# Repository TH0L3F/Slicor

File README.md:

# Slicor
Trancheuse de sable pour conçue pour l'université de Lille

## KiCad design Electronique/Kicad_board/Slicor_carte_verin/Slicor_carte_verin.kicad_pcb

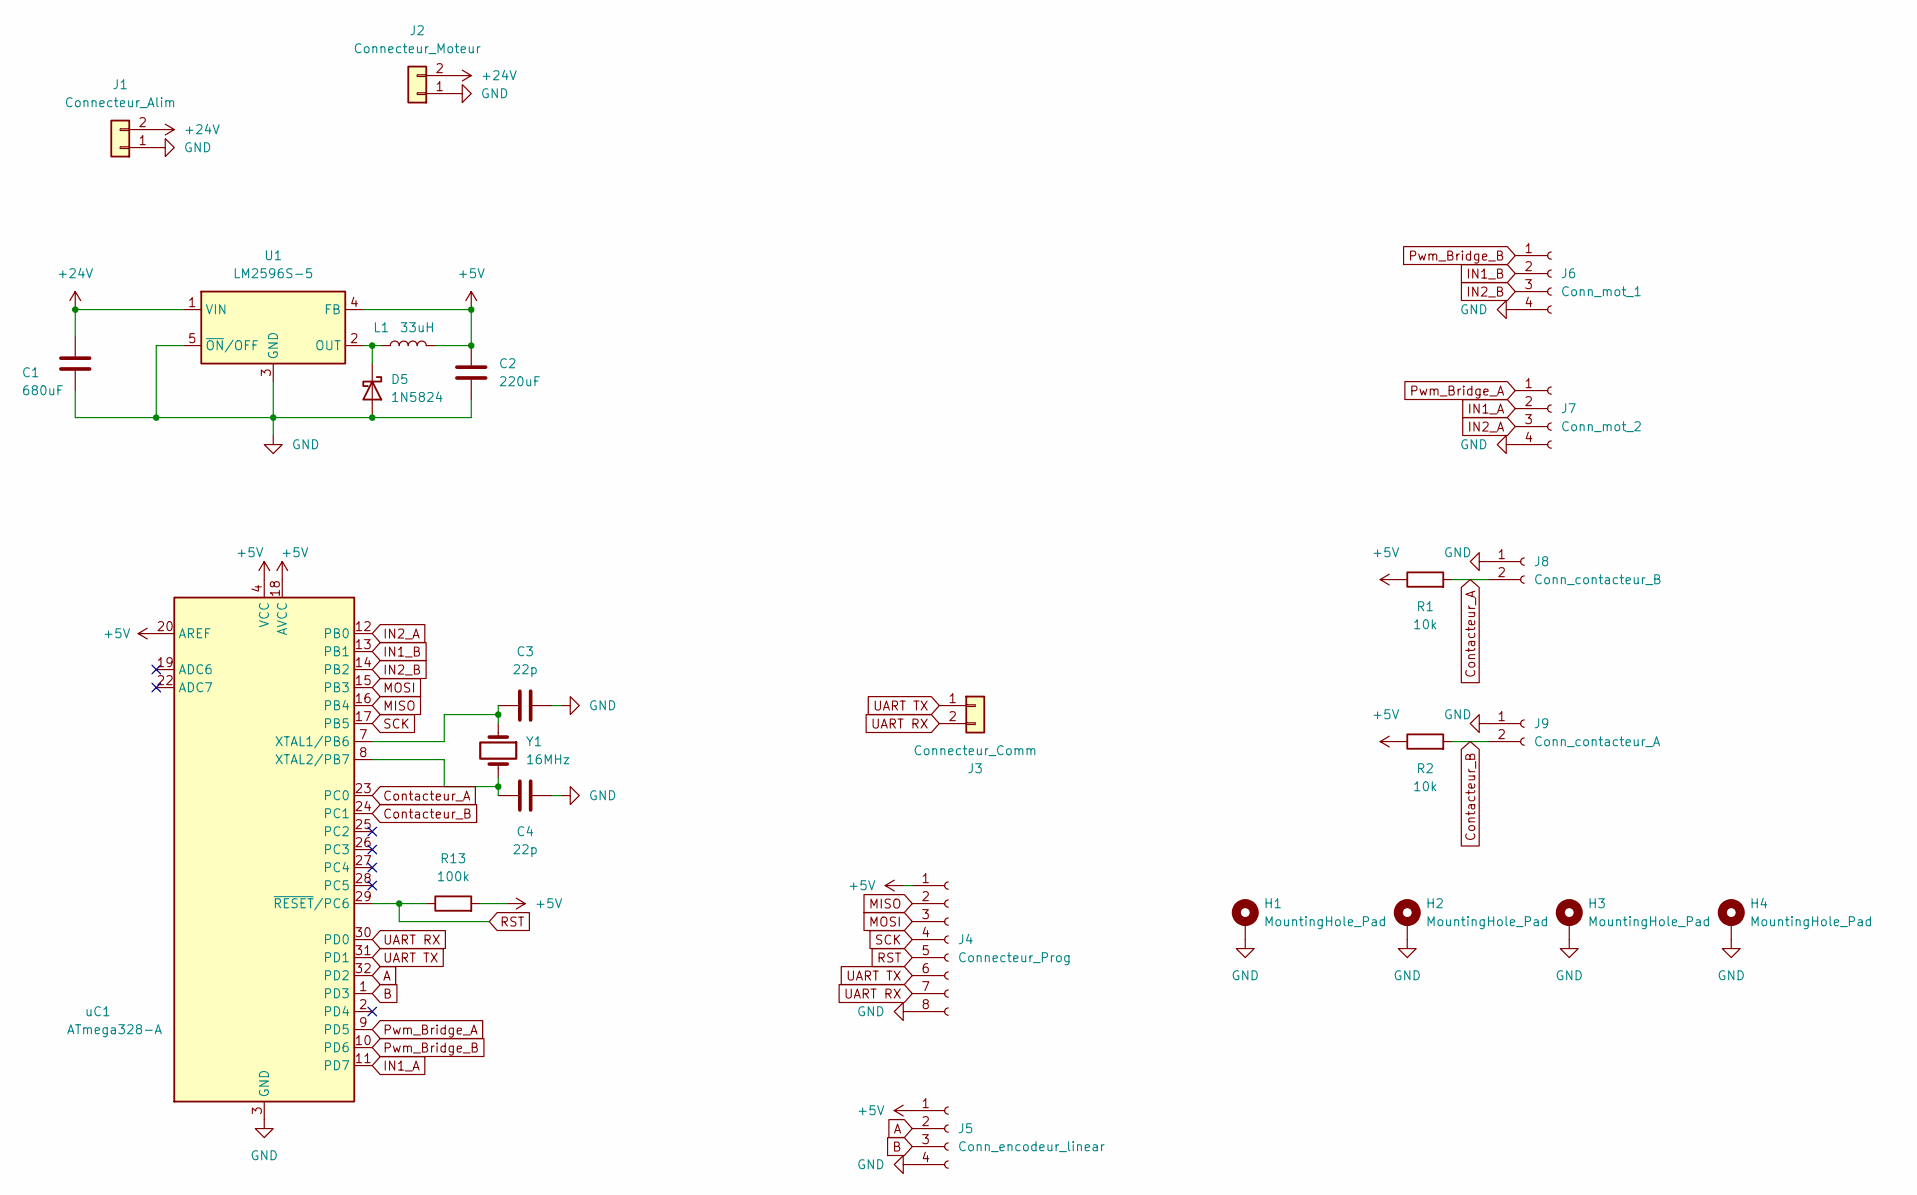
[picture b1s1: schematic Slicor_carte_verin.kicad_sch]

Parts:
C1: 680uF; C_Elec_10x10.2
C2: 220uF; C_Elec_10x10.2
C3, C4: 22p; C_01005_0402Metric
D5: 1N5824; D_SOD-128
H1, H2, H3, H4: MountingHole_Pad; MountingHole_4mm_Pad_Via
J1: Connecteur_Alim; TerminalBlock_bornier-2_P5.08mm
J2: Connecteur_Moteur; TerminalBlock_bornier-2_P5.08mm
J3: Connecteur_Comm; JST_XH_B2B-XH-A_1x02_P2.50mm_Vertical
J4: Connecteur_Prog; PinHeader_1x08_P2.54mm_Vertical
J5: Conn_encodeur_linear; JST_XH_B4B-XH-A_1x04_P2.50mm_Vertical
J6: Conn_mot_1; JST_XH_B4B-XH-A_1x04_P2.50mm_Vertical
J7: Conn_mot_2; JST_XH_B4B-XH-A_1x04_P2.50mm_Vertical
J8: Conn_contacteur_B; JST_XH_B2B-XH-A_1x02_P2.50mm_Vertical
J9: Conn_contacteur_A; JST_XH_B2B-XH-A_1x02_P2.50mm_Vertical
L1: 33uH; L_7.3x7.3_H4.5
R1, R2: 10k; R_1206_3216Metric
R13: 100k; R_1206_3216Metric
U1: LM2596S-5; TO-263-5_TabPin3
Y1: 16MHz; Crystal_SMD_3225-4Pin_3.2x2.5mm
uC1: ATmega328-A; TQFP-32_7x7mm_P0.8mm

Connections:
+5V: C2.1, J4.1, J5.1, L1.2, R1.1, R2.1, R13.2, U1.4 (FB), uC1.4 (VCC), uC1.6 (VCC), uC1.18 (AVCC), uC1.20 (AREF)
+24V: C1.1, J1.2, J2.2, U1.1 (VIN)
A: J5.2, uC1.32 (PD2)
B: J5.3, uC1.1 (PD3)
Contacteur_A: J8.2, R1.2, uC1.23 (PC0)
Contacteur_B: J9.2, R2.2, uC1.24 (PC1)
GND: C1.2, C2.2, C3.2, C4.2, D5.2 (A), H1.1, H2.1, H3.1, H4.1, J1.1, J2.1, J4.8, J5.4, J6.4, J7.4, J8.1, J9.1, U1.3 (GND), U1.5 (~ON/OFF), uC1.3 (GND), uC1.5 (GND), uC1.21 (GND)
IN1_A: J7.2, uC1.11 (PD7)
IN1_B: J6.2, uC1.13 (PB1)
IN2_A: J7.3, uC1.12 (PB0)
IN2_B: J6.3, uC1.14 (PB2)
MISO: J4.2, uC1.16 (PB4)
MOSI: J4.3, uC1.15 (PB3)
unnamed: C3.1, Y1.1, uC1.7 (XTAL1/PB6)
unnamed: C4.1, Y1.2, uC1.8 (XTAL2/PB7)
unnamed: D5.1 (K), L1.1, U1.2 (OUT)
Pwm_Bridge_A: J7.1, uC1.9 (PD5)
Pwm_Bridge_B: J6.1, uC1.10 (PD6)
RST: J4.5, R13.1, uC1.29 (~RESET/PC6)
SCK: J4.4, uC1.17 (PB5)
UART RX: J3.2, J4.7, uC1.30 (PD0)
UART TX: J3.1, J4.6, uC1.31 (PD1)

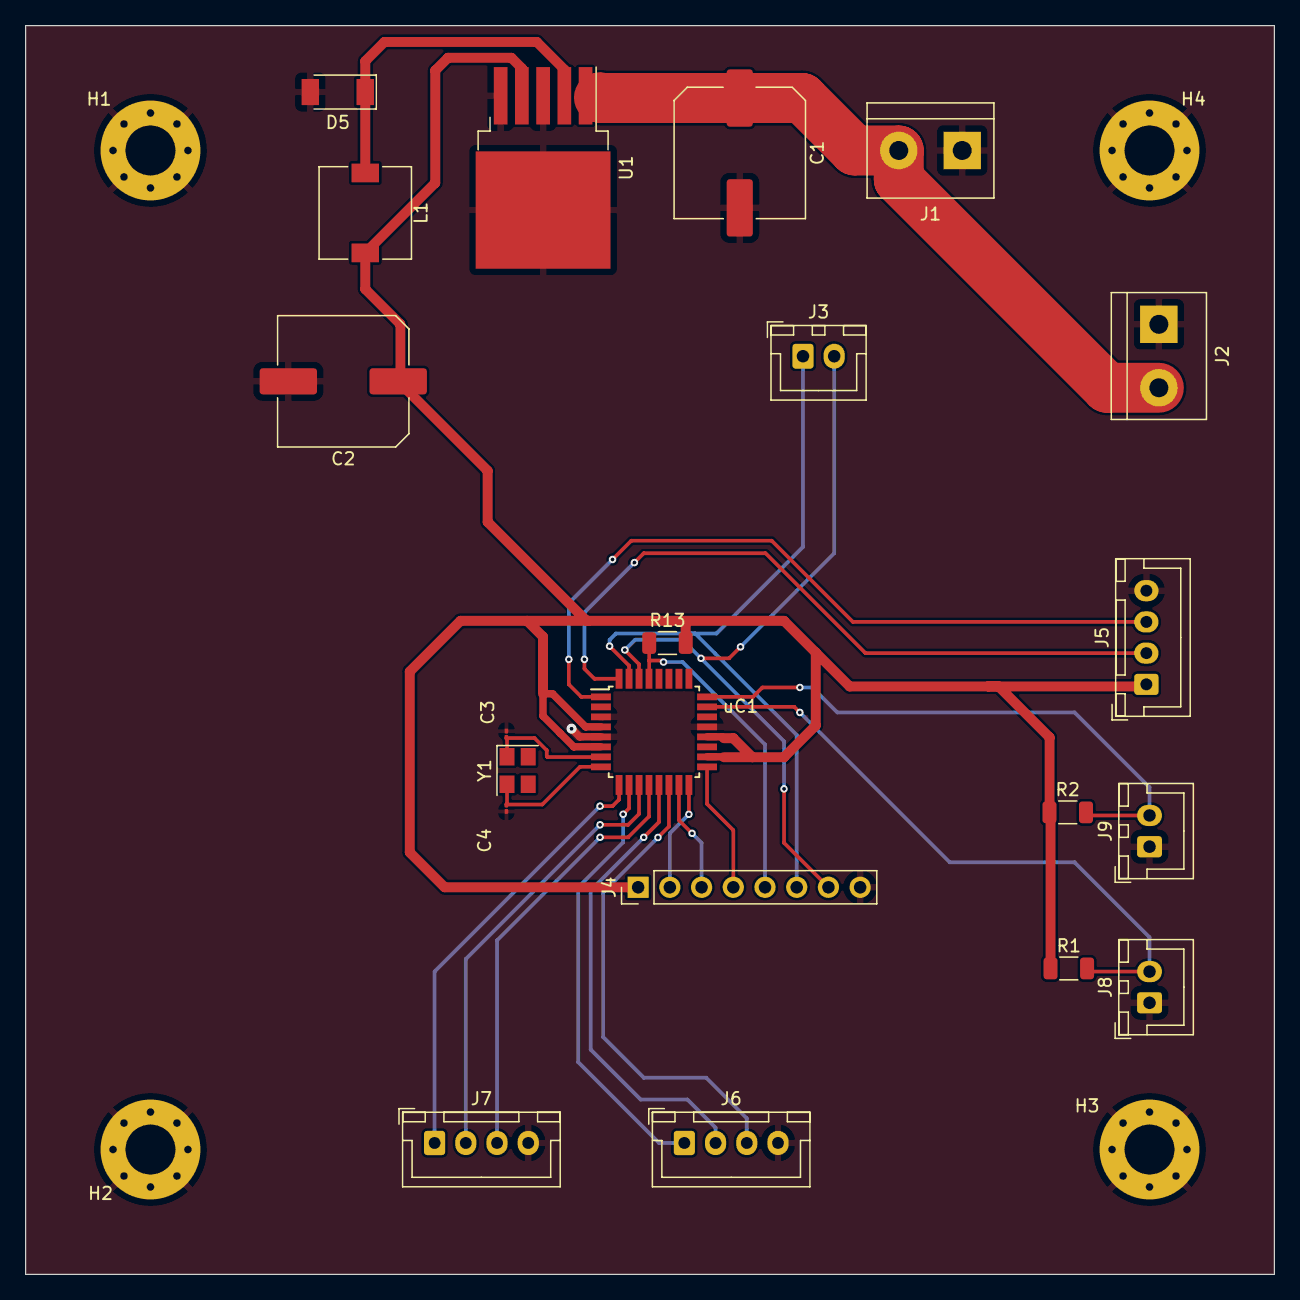
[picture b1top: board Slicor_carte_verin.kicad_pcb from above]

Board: 4 copper layers, 100.0 x 100.0 mm, 25 parts (0 on the bottom side), 22 nets.

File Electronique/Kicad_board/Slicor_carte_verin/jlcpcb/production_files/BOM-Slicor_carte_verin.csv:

Comment,Designator,Footprint,LCSC
16MHz,Y1,Crystal_SMD_3225-4Pin_3.2x2.5mm,C13738
ATmega328-A,uC1,TQFP-32_7x7mm_P0.8mm,C14877
22p,"C3,C4",C_01005_0402Metric,C1555
100k,R13,R_1206_3216Metric,C17900
10k,"R1,R2",R_1206_3216Metric,C17902
LM2596S-5,U1,TO-263-5_TabPin3,C194349
1N5824,D5,D_SOD-128,C2766156
680uF,C1,C_Elec_10x10.2,C335987
220uF,C2,C_Elec_10x10.2,C393833
33uH,L1,L_7.3x7.3_H4.5,C514809
Conn_encodeur_linear,J5,JST_XH_B4B-XH-A_1x04_P2.50mm_Vertical,
Connecteur_Comm,J3,JST_XH_B2B-XH-A_1x02_P2.50mm_Vertical,
Conn_mot_2,J7,JST_XH_B4B-XH-A_1x04_P2.50mm_Vertical,
Conn_mot_1,J6,JST_XH_B4B-XH-A_1x04_P2.50mm_Vertical,
Connecteur_Moteur,J2,TerminalBlock_bornier-2_P5.08mm,
MountingHole_Pad,H2,MountingHole_4mm_Pad_Via,
Connecteur_Alim,J1,TerminalBlock_bornier-2_P5.08mm,
MountingHole_Pad,H4,MountingHole_4mm_Pad_Via,
MountingHole_Pad,H1,MountingHole_4mm_Pad_Via,
Connecteur_Prog,J4,PinHeader_1x08_P2.54mm_Vertical,
MountingHole_Pad,H3,MountingHole_4mm_Pad_Via,
Conn_contacteur_A,J9,JST_XH_B2B-XH-A_1x02_P2.50mm_Vertical,
Conn_contacteur_B,J8,JST_XH_B2B-XH-A_1x02_P2.50mm_Vertical,

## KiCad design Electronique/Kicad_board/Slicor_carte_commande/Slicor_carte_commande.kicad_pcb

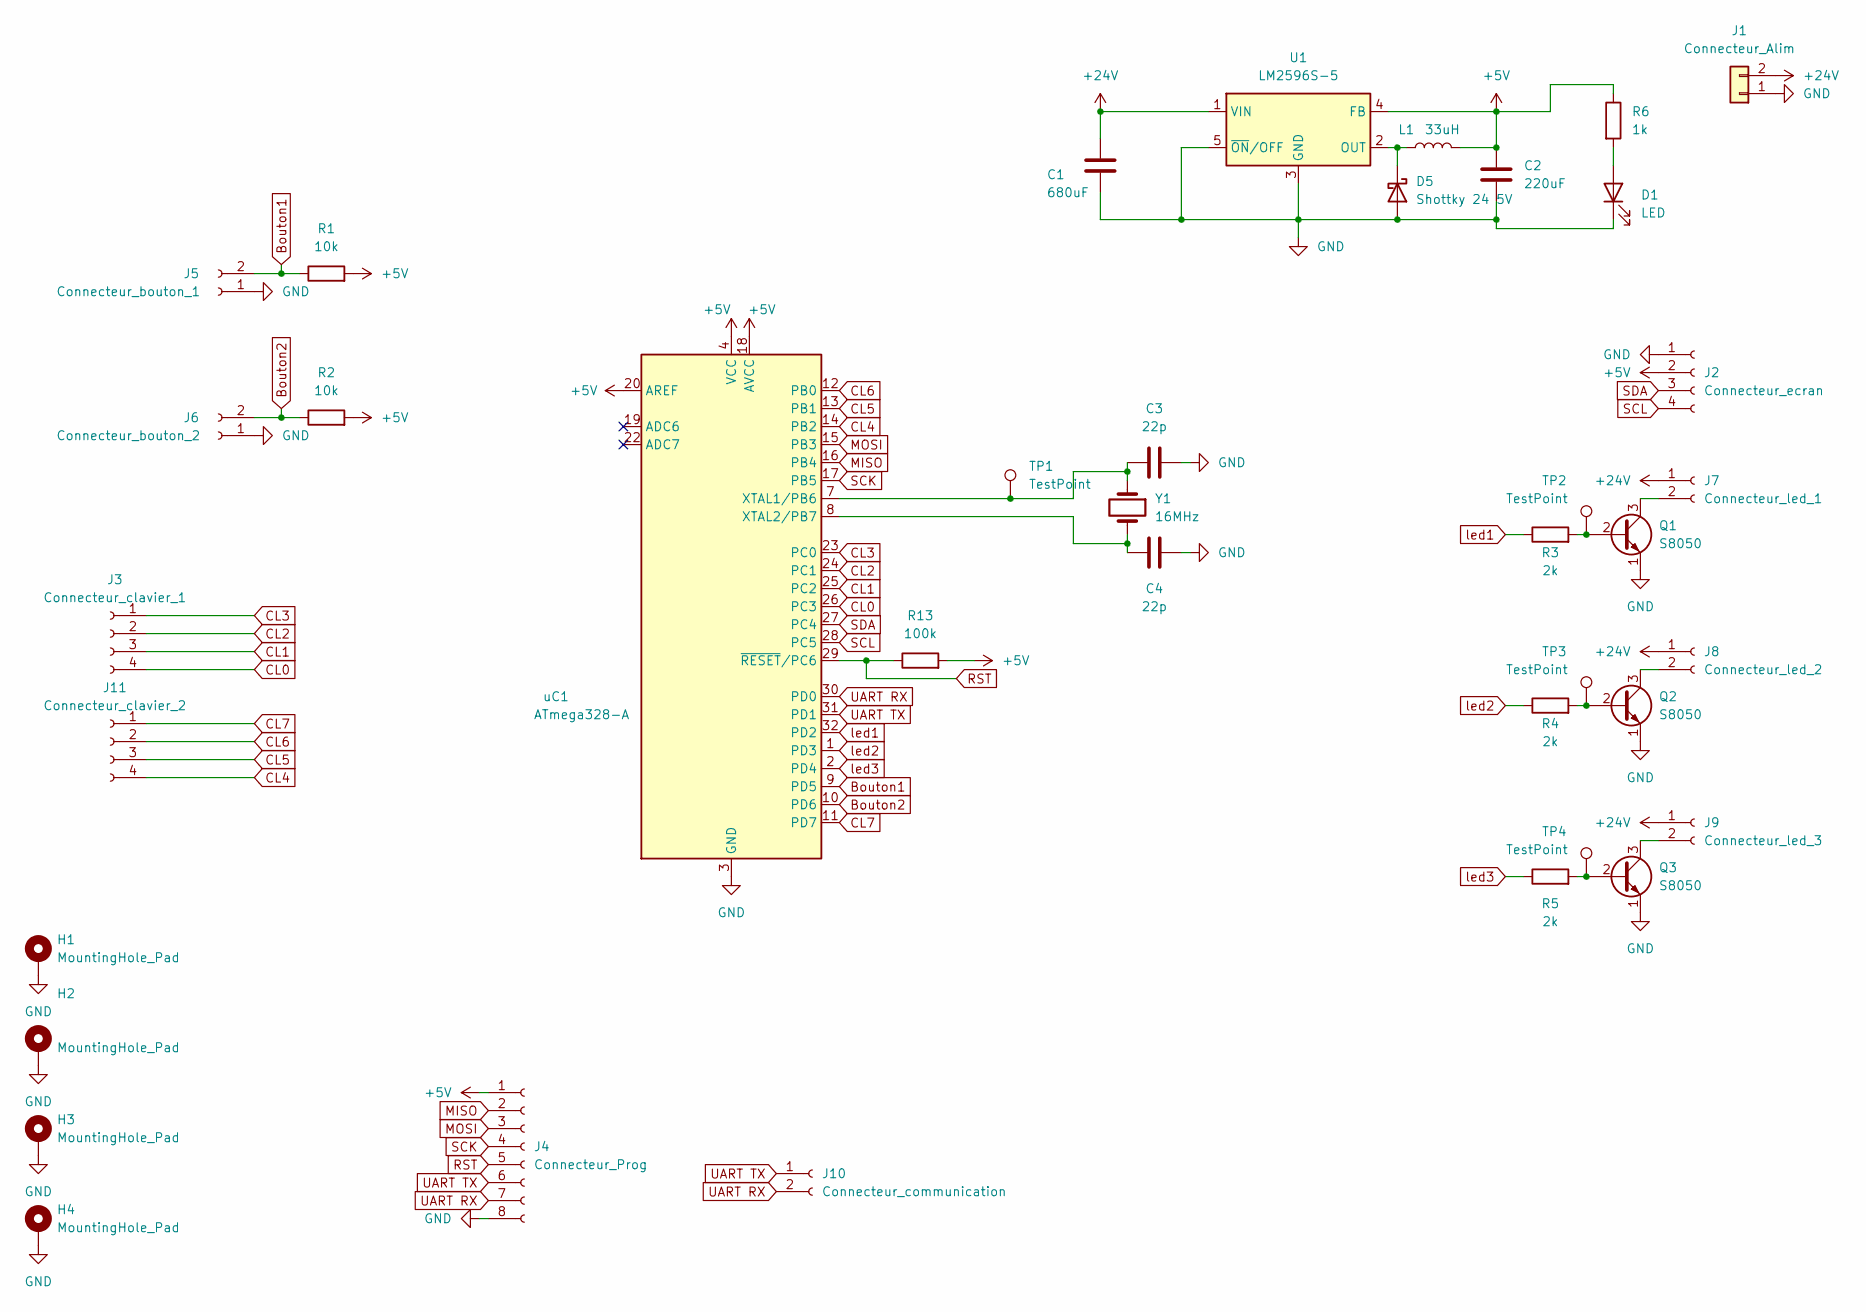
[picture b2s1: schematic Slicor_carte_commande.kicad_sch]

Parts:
C1: 680uF; C_Elec_10x10.2
C2: 220uF; C_Elec_10x10.2
C3, C4: 22p; C_0402_1005Metric
D1: LED; LED_0805_2012Metric
D5: Shottky 24 5V; D_SOD-128
H1, H2, H3, H4: MountingHole_Pad; MountingHole_4.3mm_M4_DIN965_Pad
J1: Connecteur_Alim; TerminalBlock_bornier-2_P5.08mm
J2: Connecteur_ecran; JST_XH_B4B-XH-A_1x04_P2.50mm_Vertical
J3: Connecteur_clavier_1; JST_XH_S4B-XH-A_1x04_P2.50mm_Horizontal
J4: Connecteur_Prog; PinHeader_1x08_P2.54mm_Vertical
J5: Connecteur_bouton_1; JST_XH_B2B-XH-A_1x02_P2.50mm_Vertical
J6: Connecteur_bouton_2; JST_XH_B2B-XH-A_1x02_P2.50mm_Vertical
J7: Connecteur_led_1; JST_XH_B2B-XH-A_1x02_P2.50mm_Vertical
J8: Connecteur_led_2; JST_XH_B2B-XH-A_1x02_P2.50mm_Vertical
J9: Connecteur_led_3; JST_XH_B2B-XH-A_1x02_P2.50mm_Vertical
J10: Connecteur_communication; JST_XH_B2B-XH-A_1x02_P2.50mm_Vertical
J11: Connecteur_clavier_2; JST_XH_S4B-XH-A_1x04_P2.50mm_Horizontal
L1: 33uH; L_7.3x7.3_H4.5
Q1, Q2, Q3: S8050; SOT-23-3
R1, R2: 10k; R_1206_3216Metric
R3, R4, R5: 2k; R_1206_3216Metric
R6: 1k; R_1206_3216Metric
R13: 100k; R_1206_3216Metric
TP1, TP2, TP3, TP4: TestPoint; TestPoint_Pad_1.5x1.5mm
U1: LM2596S-5; TO-263-5_TabPin3
Y1: 16MHz; Crystal_SMD_3225-4Pin_3.2x2.5mm
uC1: ATmega328-A; TQFP-32_7x7mm_P0.8mm

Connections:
+5V: C2.1, J2.2, J4.1, L1.2, R1.2, R2.2, R6.1, R13.2, U1.4 (FB), uC1.4 (VCC), uC1.6 (VCC), uC1.18 (AVCC), uC1.20 (AREF)
+24V: C1.1, J1.2, J7.1, J8.1, J9.1, U1.1 (VIN)
Bouton1: J5.2, R1.1, uC1.9 (PD5)
Bouton2: J6.2, R2.1, uC1.10 (PD6)
CL0: J3.4, uC1.26 (PC3)
CL1: J3.3, uC1.25 (PC2)
CL2: J3.2, uC1.24 (PC1)
CL3: J3.1, uC1.23 (PC0)
CL4: J11.4, uC1.14 (PB2)
CL5: J11.3, uC1.13 (PB1)
CL6: J11.2, uC1.12 (PB0)
CL7: J11.1, uC1.11 (PD7)
GND: C1.2, C2.2, C3.2, C4.2, D1.1 (K), D5.2 (A), H1.1, H2.1, H3.1, H4.1, J1.1, J2.1, J4.8, J5.1, J6.1, Q1.1 (E), Q2.1 (E), Q3.1 (E), U1.3 (GND), U1.5 (~ON/OFF), uC1.3 (GND), uC1.5 (GND), uC1.21 (GND); also elsewhere on the board
MISO: J4.2, uC1.16 (PB4)
MOSI: J4.3, uC1.15 (PB3)
unnamed: C3.1, TP1.1, Y1.1, uC1.7 (XTAL1/PB6)
unnamed: C4.1, Y1.2, uC1.8 (XTAL2/PB7)
unnamed: D1.2 (A), R6.2
unnamed: D5.1 (K), L1.1, U1.2 (OUT)
unnamed: J7.2, Q1.3 (C)
unnamed: J8.2, Q2.3 (C)
unnamed: J9.2, Q3.3 (C)
unnamed: Q1.2 (B), R3.2, TP2.1
unnamed: Q2.2 (B), R4.2, TP3.1
unnamed: Q3.2 (B), R5.2, TP4.1
RST: J4.5, R13.1, uC1.29 (~RESET/PC6)
SCK: J4.4, uC1.17 (PB5)
SCL: J2.4, uC1.28 (PC5)
SDA: J2.3, uC1.27 (PC4)
UART RX: J4.7, J10.2, uC1.30 (PD0)
UART TX: J4.6, J10.1, uC1.31 (PD1)
led1: R3.1, uC1.32 (PD2)
led2: R4.1, uC1.1 (PD3)
led3: R5.1, uC1.2 (PD4)

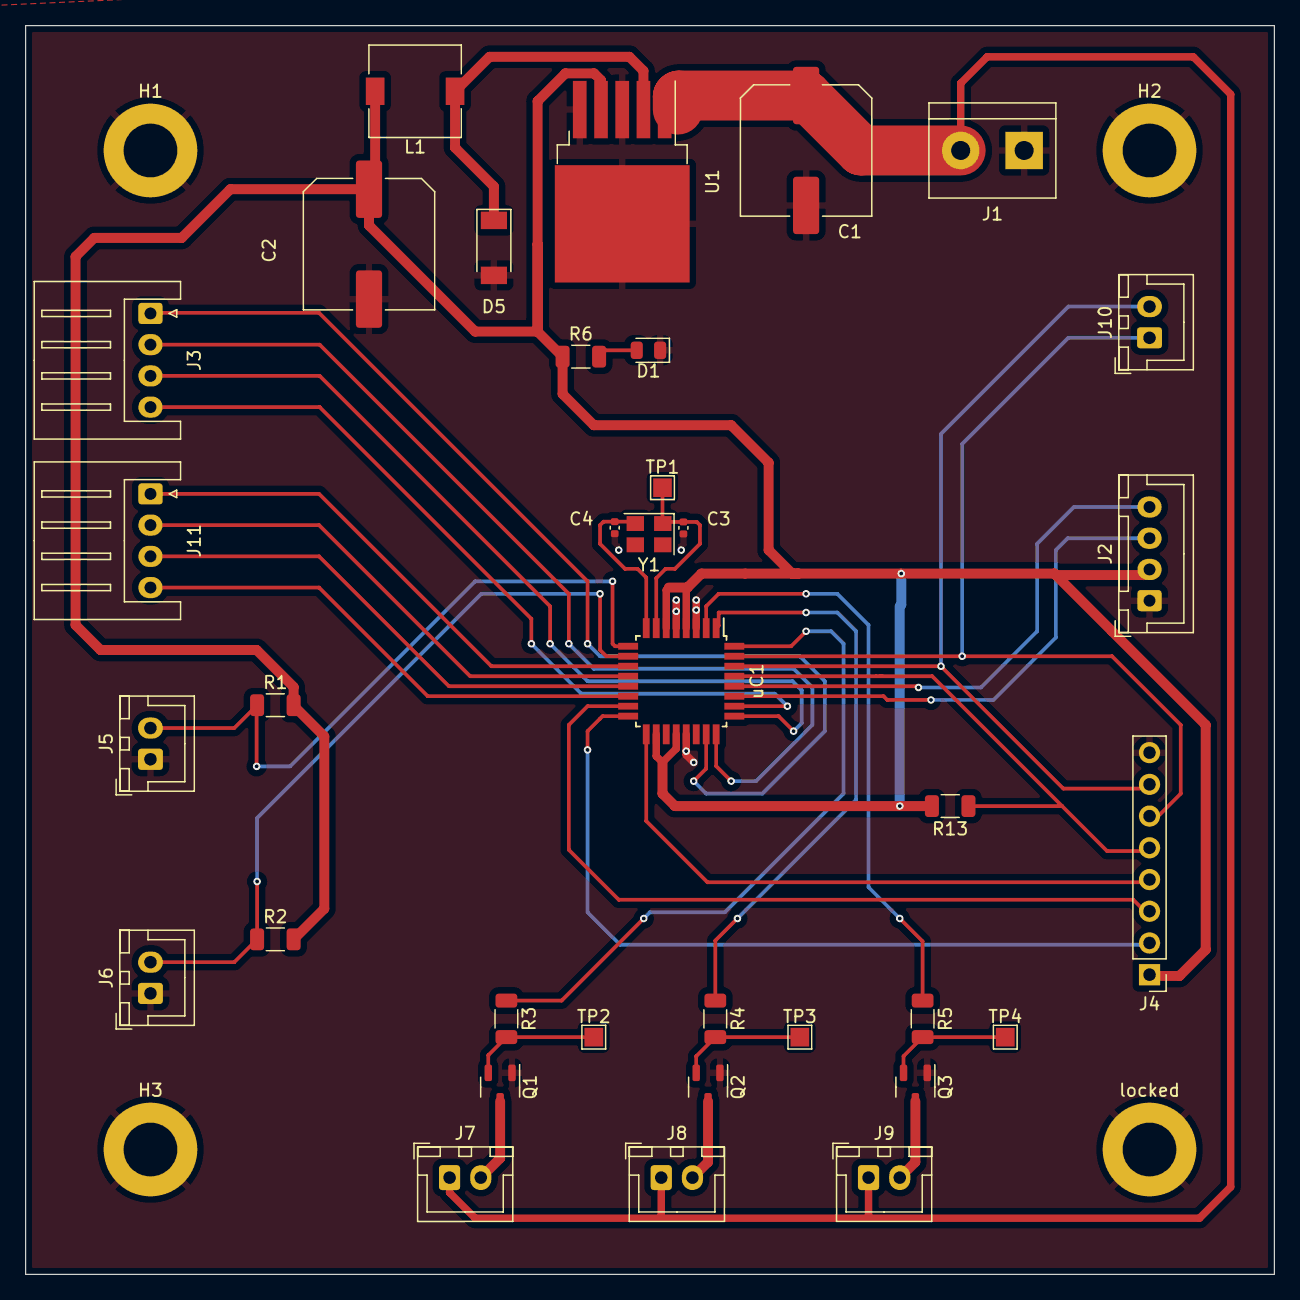
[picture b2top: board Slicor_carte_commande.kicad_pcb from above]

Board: 4 copper layers, 100.0 x 100.0 mm, 39 parts (0 on the bottom side), 34 nets.

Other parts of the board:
locked: MountingHole_Pad; MountingHole_4.3mm_M4_DIN965_Pad

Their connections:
GND: locked.1; also elsewhere on the board

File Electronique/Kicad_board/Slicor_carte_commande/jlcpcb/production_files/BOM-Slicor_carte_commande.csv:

Comment,Designator,Footprint,LCSC
16MHz,Y1,Crystal_SMD_3225-4Pin_3.2x2.5mm,C13738
ATmega328-A,uC1,TQFP-32_7x7mm_P0.8mm,C14877
22p,"C3,C4",C_0402_1005Metric,C1555
100k,R13,R_1206_3216Metric,C17900
10k,"R1,R2",R_1206_3216Metric,C17902
2k,"R3,R4,R5",R_1206_3216Metric,C17944
LM2596S-5,U1,TO-263-5_TabPin3,C194349
S8050,"Q1,Q2,Q3",SOT-23-3,C2146
Shottky 24 5V,D5,D_SOD-128,C2766156
680uF,C1,C_Elec_10x10.2,C335987
220uF,C2,C_Elec_10x10.2,C393833
1k,R6,R_1206_3216Metric,C4410
33uH,L1,L_7.3x7.3_H4.5,C514809
LED,D1,LED_0805_2012Metric,C84256
TestPoint,TP4,TestPoint_Pad_1.5x1.5mm,
TestPoint,TP3,TestPoint_Pad_1.5x1.5mm,
TestPoint,TP2,TestPoint_Pad_1.5x1.5mm,
TestPoint,TP1,TestPoint_Pad_1.5x1.5mm,
Connecteur_Alim,J1,TerminalBlock_bornier-2_P5.08mm,
Connecteur_bouton_1,J5,JST_XH_B2B-XH-A_1x02_P2.50mm_Vertical,
Connecteur_led_3,J9,JST_XH_B2B-XH-A_1x02_P2.50mm_Vertical,
Connecteur_ecran,J2,JST_XH_B4B-XH-A_1x04_P2.50mm_Vertical,
Connecteur_Prog,J4,PinHeader_1x08_P2.54mm_Vertical,
Connecteur_led_2,J8,JST_XH_B2B-XH-A_1x02_P2.50mm_Vertical,
Connecteur_clavier_1,J3,JST_XH_S4B-XH-A_1x04_P2.50mm_Horizontal,
MountingHole_Pad,H1,MountingHole_4.3mm_M4_DIN965_Pad,
Connecteur_communication,J10,JST_XH_B2B-XH-A_1x02_P2.50mm_Vertical,
Connecteur_led_1,J7,JST_XH_B2B-XH-A_1x02_P2.50mm_Vertical,
MountingHole_Pad,H4,MountingHole_4.3mm_M4_DIN965_Pad,
Connecteur_bouton_2,J6,JST_XH_B2B-XH-A_1x02_P2.50mm_Vertical,
MountingHole_Pad,H3,MountingHole_4.3mm_M4_DIN965_Pad,
MountingHole_Pad,H2,MountingHole_4.3mm_M4_DIN965_Pad,
Connecteur_clavier_2,J11,JST_XH_S4B-XH-A_1x04_P2.50mm_Horizontal,

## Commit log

2023-05-13 Modif du README
2023-05-13 Rename README.md to readme.md
2023-05-13 modif readme
2023-05-20 Ajout de la liste des choses qui restent à faire
2023-05-20 Mise à jour du readme et du manuel
2023-05-21 test
2023-05-21 ajout au readme la méthode de programmation
2023-05-25 Update readme.md
    correction faute
